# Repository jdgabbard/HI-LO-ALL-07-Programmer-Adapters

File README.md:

# HI-LO-ALL-07-Programmer-Adapters
Reverse engineered programming adapters for the ALL-07 Programmer

The purpose of this repository is to find, and redesign programming adapters for the ALL-03, ALL-07, and ALL-11 device programmers from HI-LO Systems.  Owners of such devices adapters are encouraged to provide schematics, or to "lend" devices for the purpose of creating schematics which can then be used to redesign these boards.

The reason such a project is needed is that these are very capable programmers for a multitude of older devices.  And with the clones of the programming adapters being made available, or the gerbers to create one's own, this gives owners of these programmers more reach in their ability to repair and work on legacy systems.

Currently looking for schematics for any adapters for the HI-LO systems programmers, or their "PAC" adapters: PAC-DIP48, PAC-DIP40, etc.  However, the ADP-EPM7128E-PL or ADP-EMP7128-PL is high up on the priority list.

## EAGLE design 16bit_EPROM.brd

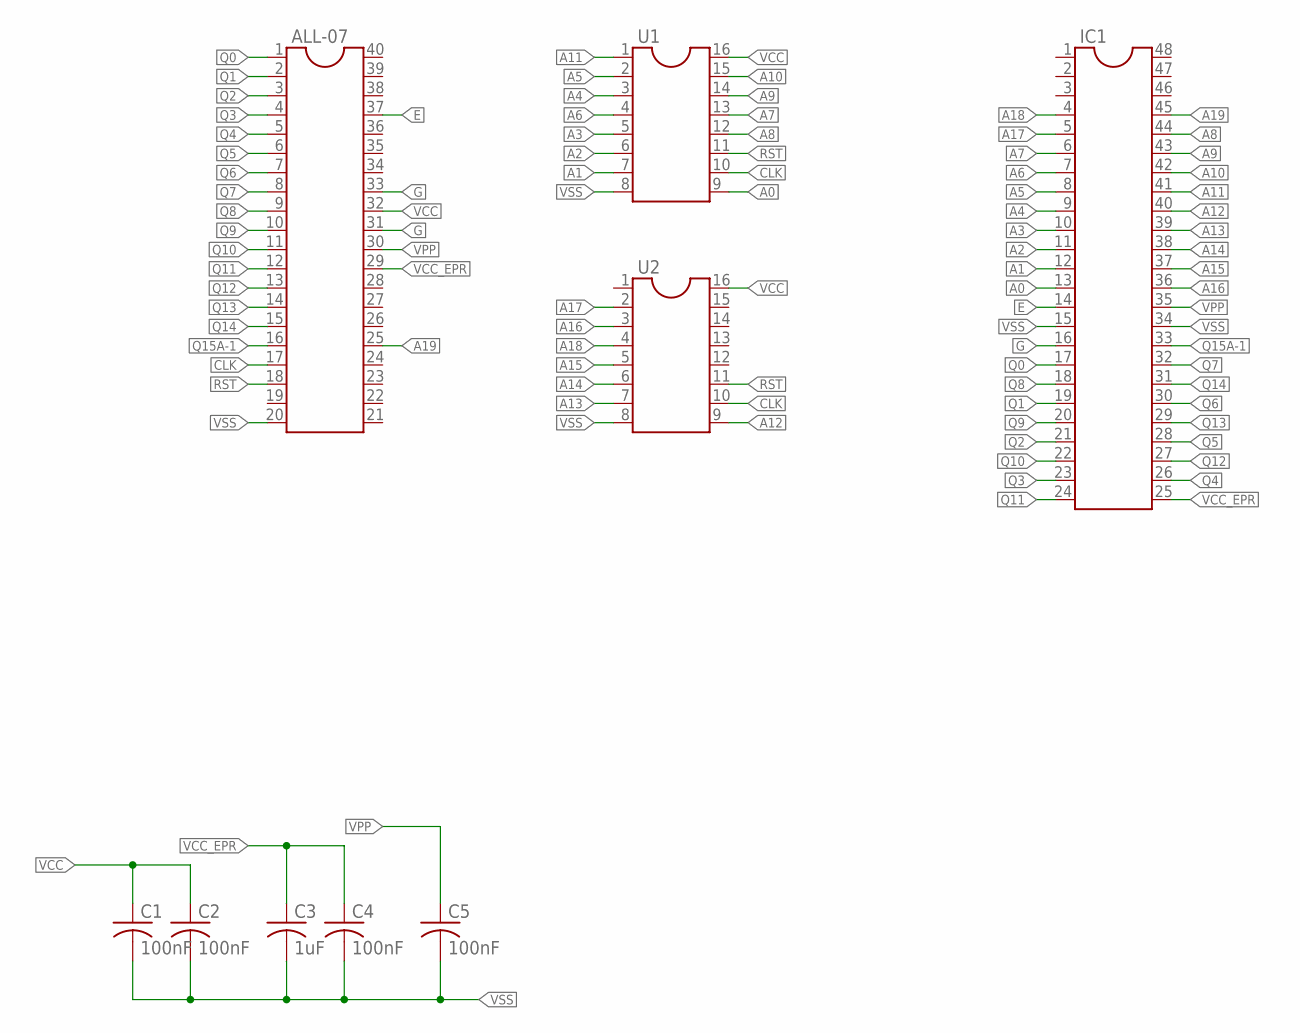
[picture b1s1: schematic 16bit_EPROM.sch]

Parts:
ALL-07: DIL40
C1, C2, C4, C5: 100nF; C050-025X075
C3: 1uF; C050-025X075
IC1: DIL48
U1, U2: DIL16

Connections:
A0: IC1.13, U1.9
A1: IC1.12, U1.7
A2: IC1.11, U1.6
A3: IC1.10, U1.5
A4: IC1.9, U1.3
A5: IC1.8, U1.2
A6: IC1.7, U1.4
A7: IC1.6, U1.13
A8: IC1.44, U1.12
A9: IC1.43, U1.14
A10: IC1.42, U1.15
A11: IC1.41, U1.1
A12: IC1.40, U2.9
A13: IC1.39, U2.7
A14: IC1.38, U2.6
A15: IC1.37, U2.5
A16: IC1.36, U2.3
A17: IC1.5, U2.2
A18: IC1.4, U2.4
A19: ALL-07.25, IC1.45
CLK: ALL-07.17, U1.10, U2.10
E: ALL-07.37, IC1.14
G: ALL-07.31, ALL-07.33, IC1.16
Q0: ALL-07.1, IC1.17
Q1: ALL-07.2, IC1.19
Q2: ALL-07.3, IC1.21
Q3: ALL-07.4, IC1.23
Q4: ALL-07.5, IC1.26
Q5: ALL-07.6, IC1.28
Q6: ALL-07.7, IC1.30
Q7: ALL-07.8, IC1.32
Q8: ALL-07.9, IC1.18
Q9: ALL-07.10, IC1.20
Q10: ALL-07.11, IC1.22
Q11: ALL-07.12, IC1.24
Q12: ALL-07.13, IC1.27
Q13: ALL-07.14, IC1.29
Q14: ALL-07.15, IC1.31
Q15A-1: ALL-07.16, IC1.33
RST: ALL-07.18, U1.11, U2.11
VCC: ALL-07.32, C1.1, C2.1, U1.16, U2.16
VCC_EPR: ALL-07.29, C3.1, C4.1, IC1.25
VPP: ALL-07.30, C5.1, IC1.35
VSS: ALL-07.20, C1.2, C2.2, C3.2, C4.2, C5.2, IC1.15, IC1.34, U1.8, U2.8

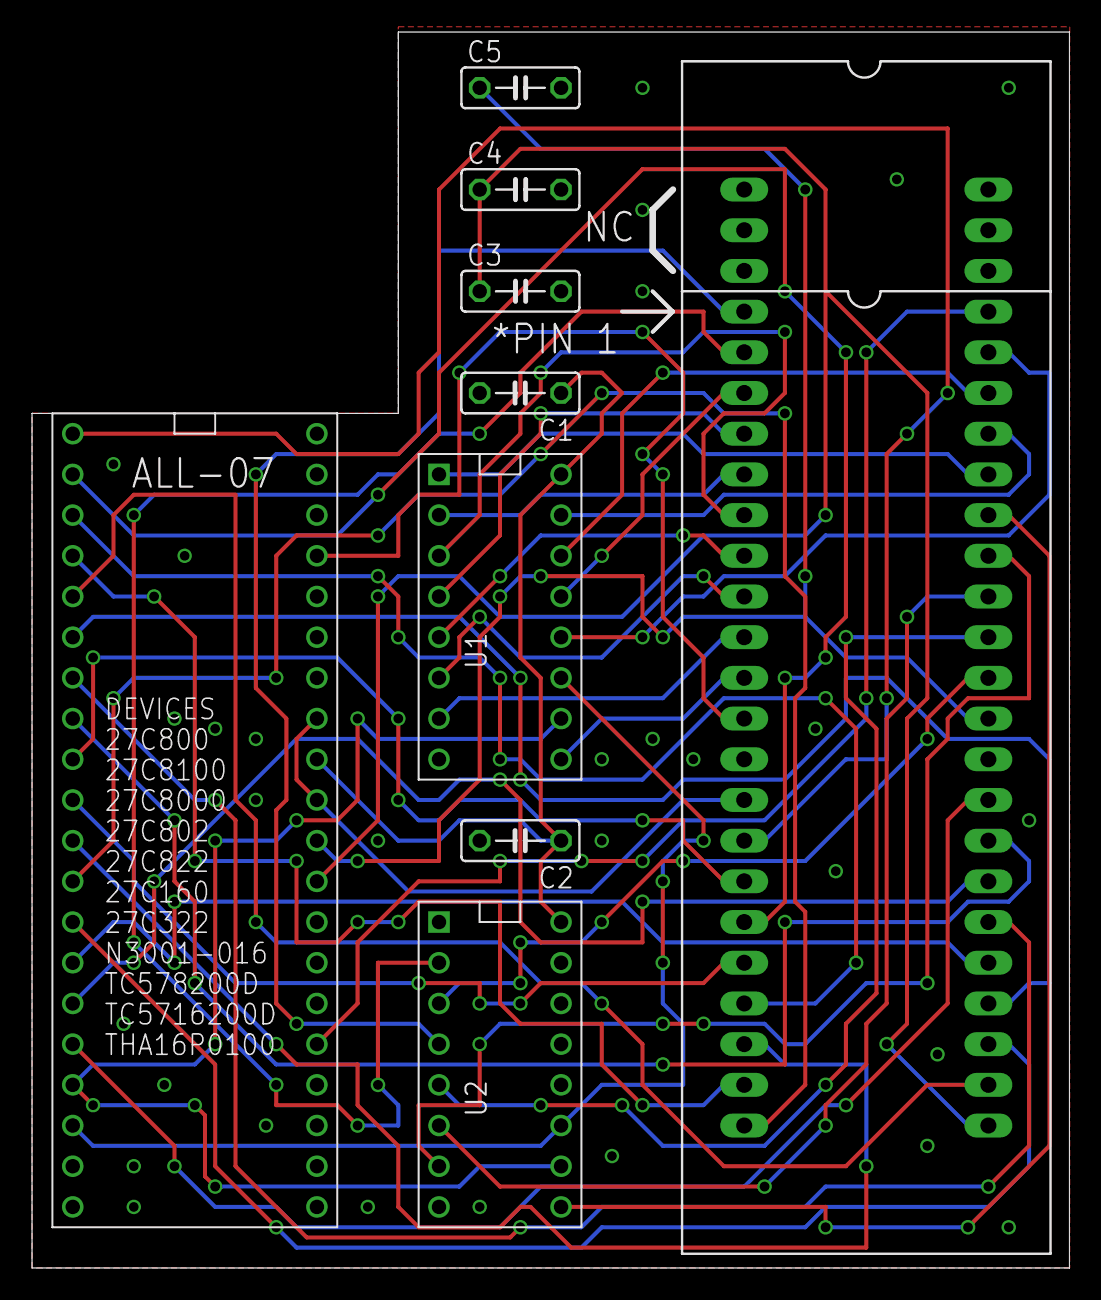
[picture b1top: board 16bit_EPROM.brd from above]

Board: 2 copper layers, 64.8 x 77.1 mm, 9 parts (0 on the bottom side), 44 nets.

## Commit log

2020-07-30 EP42 16bit EPROM Adapter
2020-07-30 README.md for EP42
